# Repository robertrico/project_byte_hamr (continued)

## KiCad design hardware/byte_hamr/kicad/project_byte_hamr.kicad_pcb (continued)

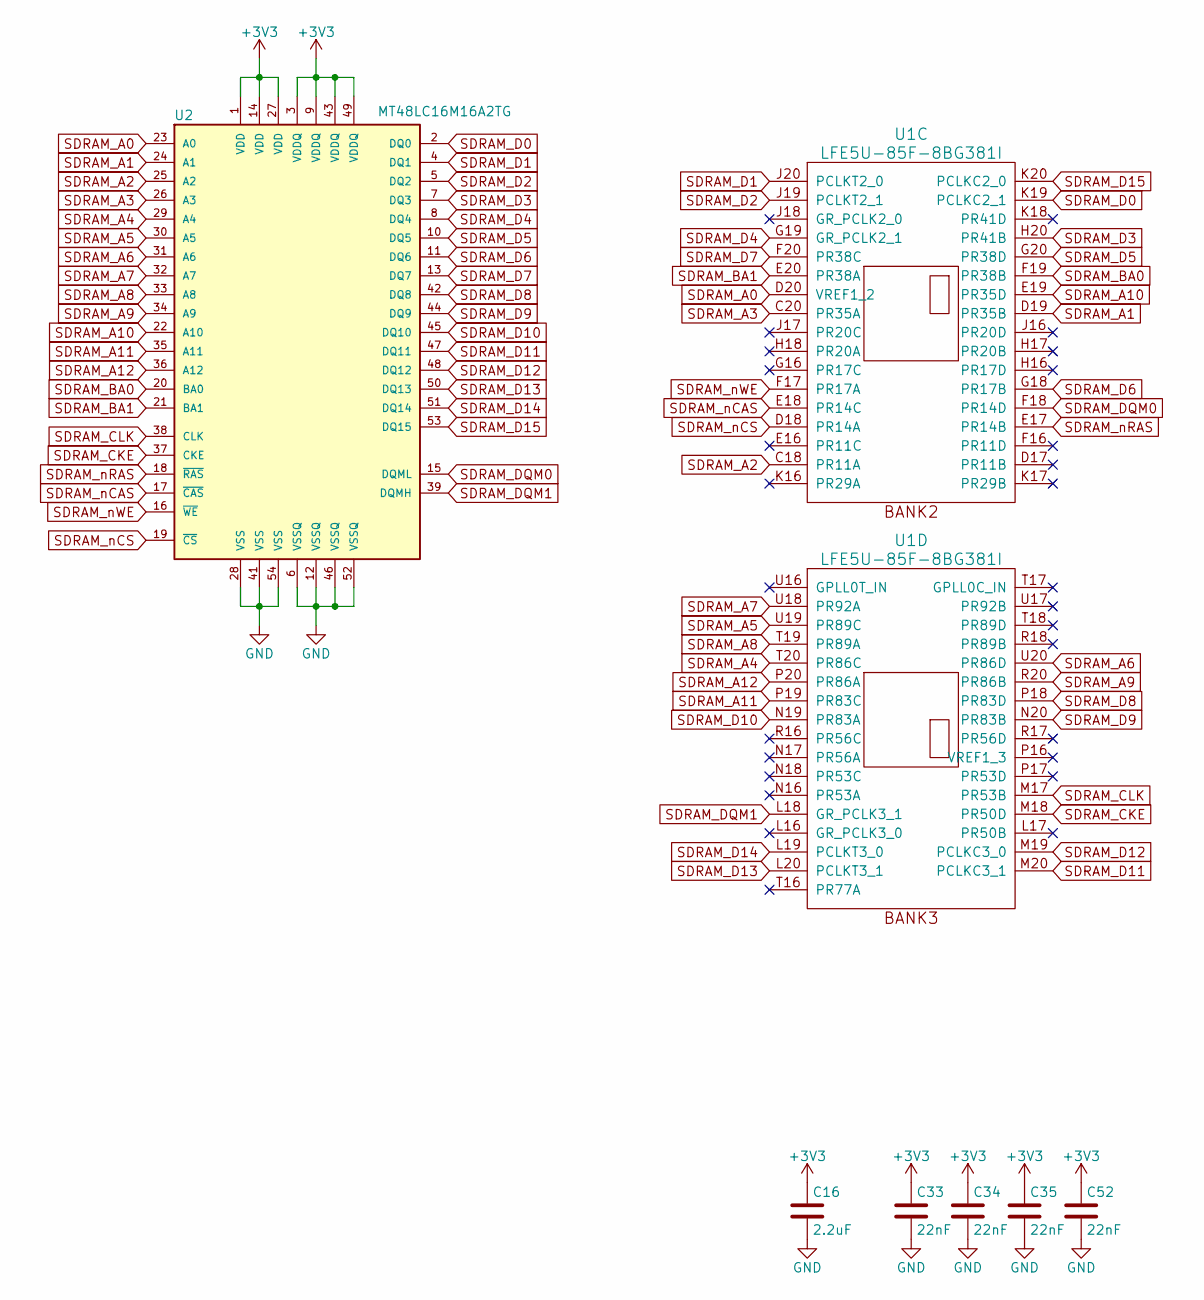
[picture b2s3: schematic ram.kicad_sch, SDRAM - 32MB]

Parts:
C16: 2.2uF; C_0805_2012Metric; MPN CL21B225KOFNNNE
C33, C34, C35, C52: 22nF; C_0603_1608Metric; MPN CX0603MRX7R8BB223
U1: LFE5U-85F-8BG381I; BGA-381_pitch0.8mm_dia0.4mm; MPN LFE5U-85F-8BG381I
U2: MT48LC16M16A2TG; TSOP54; MPN AS4C32M16SB-7TCNTR

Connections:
+3V3: C16.1, C33.1, C34.1, C35.1, C52.1, U2.1 (VDD), U2.3 (VDDQ), U2.9 (VDDQ), U2.14 (VDD), U2.27 (VDD), U2.43 (VDDQ), U2.49 (VDDQ); also elsewhere on the board
GND: C16.2, C33.2, C34.2, C35.2, C52.2, U2.6 (VSSQ), U2.12 (VSSQ), U2.28 (VSS), U2.41 (VSS), U2.46 (VSSQ), U2.52 (VSSQ), U2.54 (VSS); also elsewhere on the board
SDRAM_A0: U1.D20 (VREF1_2), U2.23 (A0)
SDRAM_A1: U1.D19 (PR35B), U2.24 (A1)
SDRAM_A2: U1.C18 (PR11A), U2.25 (A2)
SDRAM_A3: U1.C20 (PR35A), U2.26 (A3)
SDRAM_A4: U1.T20 (PR86C), U2.29 (A4)
SDRAM_A5: U1.U19 (PR89C), U2.30 (A5)
SDRAM_A6: U1.U20 (PR86D), U2.31 (A6)
SDRAM_A7: U1.U18 (PR92A), U2.32 (A7)
SDRAM_A8: U1.T19 (PR89A), U2.33 (A8)
SDRAM_A9: U1.R20 (PR86B), U2.34 (A9)
SDRAM_A10: U1.E19 (PR35D), U2.22 (A10)
SDRAM_A11: U1.P19 (PR83C), U2.35 (A11)
SDRAM_A12: U1.P20 (PR86A), U2.36 (A12)
SDRAM_BA0: U1.F19 (PR38B), U2.20 (BA0)
SDRAM_BA1: U1.E20 (PR38A), U2.21 (BA1)
SDRAM_CKE: U1.M18 (PR50D), U2.37 (CKE)
SDRAM_CLK: U1.M17 (PR53B), U2.38 (CLK)
SDRAM_D0: U1.K19 (PCLKC2_1), U2.2 (DQ0)
SDRAM_D1: U1.J20 (PCLKT2_0), U2.4 (DQ1)
SDRAM_D2: U1.J19 (PCLKT2_1), U2.5 (DQ2)
SDRAM_D3: U1.H20 (PR41B), U2.7 (DQ3)
SDRAM_D4: U1.G19 (GR_PCLK2_1), U2.8 (DQ4)
SDRAM_D5: U1.G20 (PR38D), U2.10 (DQ5)
SDRAM_D6: U1.G18 (PR17B), U2.11 (DQ6)
SDRAM_D7: U1.F20 (PR38C), U2.13 (DQ7)
SDRAM_D8: U1.P18 (PR83D), U2.42 (DQ8)
SDRAM_D9: U1.N20 (PR83B), U2.44 (DQ9)
SDRAM_D10: U1.N19 (PR83A), U2.45 (DQ10)
SDRAM_D11: U1.M20 (PCLKC3_1), U2.47 (DQ11)
SDRAM_D12: U1.M19 (PCLKC3_0), U2.48 (DQ12)
SDRAM_D13: U1.L20 (PCLKT3_1), U2.50 (DQ13)
SDRAM_D14: U1.L19 (PCLKT3_0), U2.51 (DQ14)
SDRAM_D15: U1.K20 (PCLKC2_0), U2.53 (DQ15)
SDRAM_DQM0: U1.F18 (PR14D), U2.15 (DQML)
SDRAM_DQM1: U1.L18 (GR_PCLK3_1), U2.39 (DQMH)
SDRAM_nCAS: U1.E18 (PR14C), U2.17 (~CAS)
SDRAM_nCS: U1.D18 (PR14A), U2.19 (~CS)
SDRAM_nRAS: U1.E17 (PR14B), U2.18 (~RAS)
SDRAM_nWE: U1.F17 (PR17A), U2.16 (~WE)

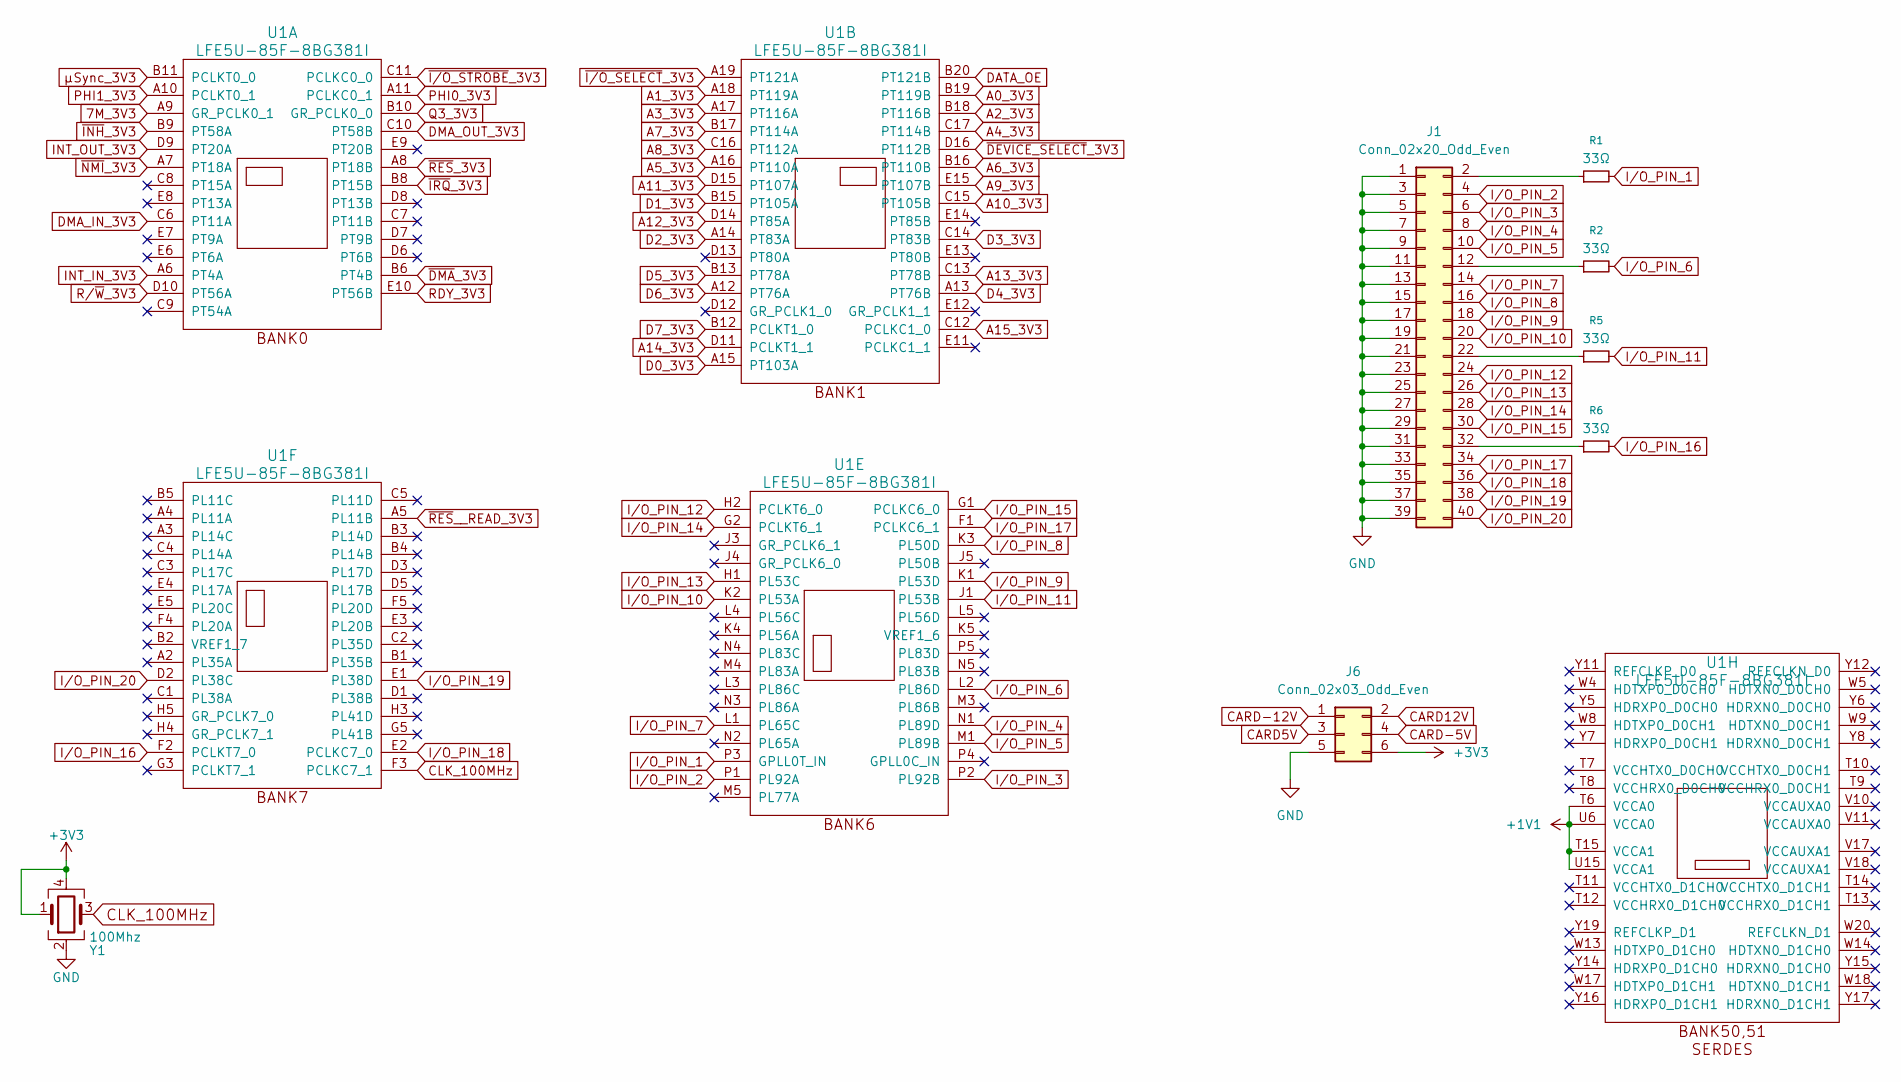
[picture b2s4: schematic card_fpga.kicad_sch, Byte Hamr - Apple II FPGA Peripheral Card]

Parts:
J1: Conn_02x20_Odd_Even; PinHeader_2x20_P2.54mm_Vertical
J6: Conn_02x03_Odd_Even; PinHeader_2x03_P2.54mm_Vertical
R1, R2, R5, R6: 33Ω; R_0603_1608Metric; MPN 0603WAF330JT5E
U1: LFE5U-85F-8BG381I; BGA-381_pitch0.8mm_dia0.4mm; MPN LFE5U-85F-8BG381I
Y1: 100Mhz; Crystal_SMD_7050_4Pads; MPN CWX813-100.0M

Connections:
7M_3V3: U1.A9 (GR_PCLK0_1); also elsewhere on the board
+1V1: U1.T6 (VCCA0), U1.T15 (VCCA1), U1.U6 (VCCA0), U1.U15 (VCCA1); also elsewhere on the board
+3V3: J6.6, Y1.1, Y1.4; also elsewhere on the board
A0_3V3: U1.B19 (PT119B); also elsewhere on the board
A1_3V3: U1.A18 (PT119A); also elsewhere on the board
A2_3V3: U1.B18 (PT116B); also elsewhere on the board
A3_3V3: U1.A17 (PT116A); also elsewhere on the board
A4_3V3: U1.C17 (PT114B); also elsewhere on the board
A5_3V3: U1.A16 (PT110A); also elsewhere on the board
A6_3V3: U1.B16 (PT110B); also elsewhere on the board
A7_3V3: U1.B17 (PT114A); also elsewhere on the board
A8_3V3: U1.C16 (PT112A); also elsewhere on the board
A9_3V3: U1.E15 (PT107B); also elsewhere on the board
A10_3V3: U1.C15 (PT105B); also elsewhere on the board
A11_3V3: U1.D15 (PT107A); also elsewhere on the board
A12_3V3: U1.D14 (PT85A); also elsewhere on the board
A13_3V3: U1.C13 (PT78B); also elsewhere on the board
A14_3V3: U1.D11 (PCLKT1_1); also elsewhere on the board
A15_3V3: U1.C12 (PCLKC1_0); also elsewhere on the board
CARD5V: J6.3; also elsewhere on the board
CARD12V: J6.2; also elsewhere on the board
CARD-5V: J6.4; also elsewhere on the board
CARD-12V: J6.1; also elsewhere on the board
CLK_100MHz: U1.F3 (PCLKC7_1), Y1.3
D0_3V3: U1.A15 (PT103A); also elsewhere on the board
D1_3V3: U1.B15 (PT105A); also elsewhere on the board
D2_3V3: U1.A14 (PT83A); also elsewhere on the board
D3_3V3: U1.C14 (PT83B); also elsewhere on the board
D4_3V3: U1.A13 (PT76B); also elsewhere on the board
D5_3V3: U1.B13 (PT78A); also elsewhere on the board
D6_3V3: U1.A12 (PT76A); also elsewhere on the board
D7_3V3: U1.B12 (PCLKT1_0); also elsewhere on the board
DATA_OE: U1.B20 (PT121B); also elsewhere on the board
DMA_IN_3V3: U1.C6 (PT11A); also elsewhere on the board
DMA_OUT_3V3: U1.C10 (PT58B); also elsewhere on the board
GND: J1.1, J1.3, J1.5, J1.7, J1.9, J1.11, J1.13, J1.15, J1.17, J1.19, J1.21, J1.23, J1.25, J1.27, J1.29, J1.31, J1.33, J1.35, J1.37, J1.39, J6.5, Y1.2; also elsewhere on the board
INT_IN_3V3: U1.A6 (PT4A); also elsewhere on the board
INT_OUT_3V3: U1.D9 (PT20A); also elsewhere on the board
I/O_PIN_1: R1.2, U1.P3 (GPLL0T_IN)
I/O_PIN_2: J1.4, U1.P1 (PL92A)
I/O_PIN_3: J1.6, U1.P2 (PL92B)
I/O_PIN_4: J1.8, U1.N1 (PL89D)
I/O_PIN_5: J1.10, U1.M1 (PL89B)
I/O_PIN_6: R2.2, U1.L2 (PL86D)
I/O_PIN_7: J1.14, U1.L1 (PL65C)
I/O_PIN_8: J1.16, U1.K3 (PL50D)
I/O_PIN_9: J1.18, U1.K1 (PL53D)
I/O_PIN_10: J1.20, U1.K2 (PL53A)
I/O_PIN_11: R5.2, U1.J1 (PL53B)
I/O_PIN_12: J1.24, U1.H2 (PCLKT6_0)
I/O_PIN_13: J1.26, U1.H1 (PL53C)
I/O_PIN_14: J1.28, U1.G2 (PCLKT6_1)
I/O_PIN_15: J1.30, U1.G1 (PCLKC6_0)
I/O_PIN_16: R6.2, U1.F2 (PCLKT7_0)
I/O_PIN_17: J1.34, U1.F1 (PCLKC6_1)
I/O_PIN_18: J1.36, U1.E2 (PCLKC7_0)
I/O_PIN_19: J1.38, U1.E1 (PL38D)
I/O_PIN_20: J1.40, U1.D2 (PL38C)
unnamed: J1.2, R1.1
unnamed: J1.12, R2.1
unnamed: J1.22, R5.1
unnamed: J1.32, R6.1
PHI0_3V3: U1.A11 (PCLKC0_1); also elsewhere on the board
PHI1_3V3: U1.A10 (PCLKT0_1); also elsewhere on the board
Q3_3V3: U1.B10 (GR_PCLK0_0); also elsewhere on the board
RDY_3V3: U1.E10 (PT56B); also elsewhere on the board
R/~W_3V3: U1.D10 (PT56A); also elsewhere on the board
~DEVICE_SELECT_3V3: U1.D16 (PT112B); also elsewhere on the board
~DMA_3V3: U1.B6 (PT4B); also elsewhere on the board
~INH_3V3: U1.B9 (PT58A); also elsewhere on the board
~IRQ_3V3: U1.B8 (PT15B); also elsewhere on the board
~I/O_SELECT_3V3: U1.A19 (PT121A); also elsewhere on the board
~I/O_STROBE_3V3: U1.C11 (PCLKC0_0); also elsewhere on the board
~NMI_3V3: U1.A7 (PT18A); also elsewhere on the board
~RES_3V3: U1.A8 (PT18B); also elsewhere on the board
~RES__READ_3V3: U1.A5 (PL11B); also elsewhere on the board
µSync_3V3: U1.B11 (PCLKT0_0); also elsewhere on the board

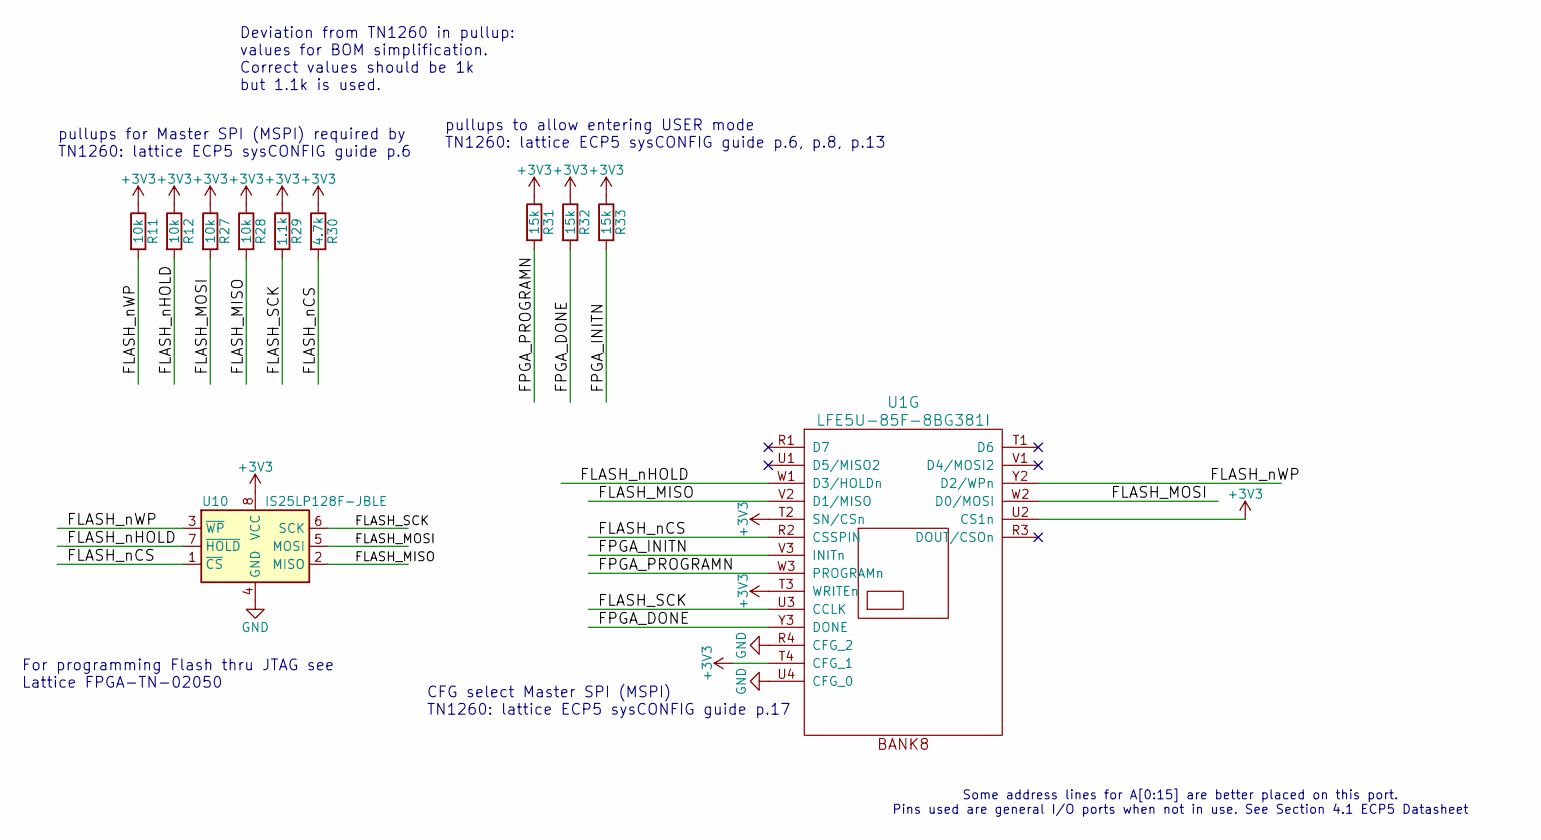
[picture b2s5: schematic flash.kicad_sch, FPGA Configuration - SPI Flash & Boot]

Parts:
R11, R12, R27, R28: 10k; R_0603_1608Metric; MPN AF0603FR-0710KL
R29: 1.1k; R_0603_1608Metric; MPN 0603WAF1101T5E
R30: 4.7k; R_0603_1608Metric; MPN AC0603FR-104K7L
R31, R32, R33: 15k; R_0603_1608Metric; MPN RC0603FR-0715KL
U1: LFE5U-85F-8BG381I; BGA-381_pitch0.8mm_dia0.4mm; MPN LFE5U-85F-8BG381I
U10: IS25LP128F-JBLE; SOA008-150-208mil; MPN IS25LP128F-JBLE

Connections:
+3V3: R11.1, R12.1, R27.1, R28.1, R29.1, R30.1, R31.1, R32.1, R33.1, U1.T2 (SN/CSn), U1.T3 (WRITEn), U1.T4 (CFG_1), U1.U2 (CS1n), U10.8 (VCC); also elsewhere on the board
/flash/FLASH_MISO: R28.2, U1.V2 (D1/MISO), U10.2 (MISO)
/flash/FLASH_MOSI: R27.2, U1.W2 (D0/MOSI), U10.5 (MOSI)
/flash/FLASH_SCK: R29.2, U1.U3 (CCLK), U10.6 (SCK)
/flash/FLASH_nCS: R30.2, U1.R2 (CSSPIN), U10.1 (~CS)
/flash/FLASH_nHOLD: R12.2, U1.W1 (D3/HOLDn), U10.7 (~HOLD)
/flash/FLASH_nWP: R11.2, U1.Y2 (D2/WPn), U10.3 (~WP)
/flash/FPGA_DONE: R32.2, U1.Y3 (DONE)
/flash/FPGA_INITN: R33.2, U1.V3 (INITn)
/flash/FPGA_PROGRAMN: R31.2, U1.W3 (PROGRAMn)
GND: U1.R4 (CFG_2), U1.U4 (CFG_0), U10.4 (GND); also elsewhere on the board

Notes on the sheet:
pullups to allow entering USER mode TN1260: lattice ECP5 sysCONFIG guide p.6, p.8, p.13
pullups for Master SPI (MSPI) required by TN1260: lattice ECP5 sysCONFIG guide p.6
Some address lines for A[0:15] are better placed on this port. Pins used are general I/O ports when not in use. See Section 4.1 ECP5 Datasheet
Deviation from TN1260 in pullup: values for BOM simplification. Correct values should be 1k but 1.1k is used.
CFG select Master SPI (MSPI) TN1260: lattice ECP5 sysCONFIG guide p.17
For programming Flash thru JTAG see Lattice FPGA-TN-02050

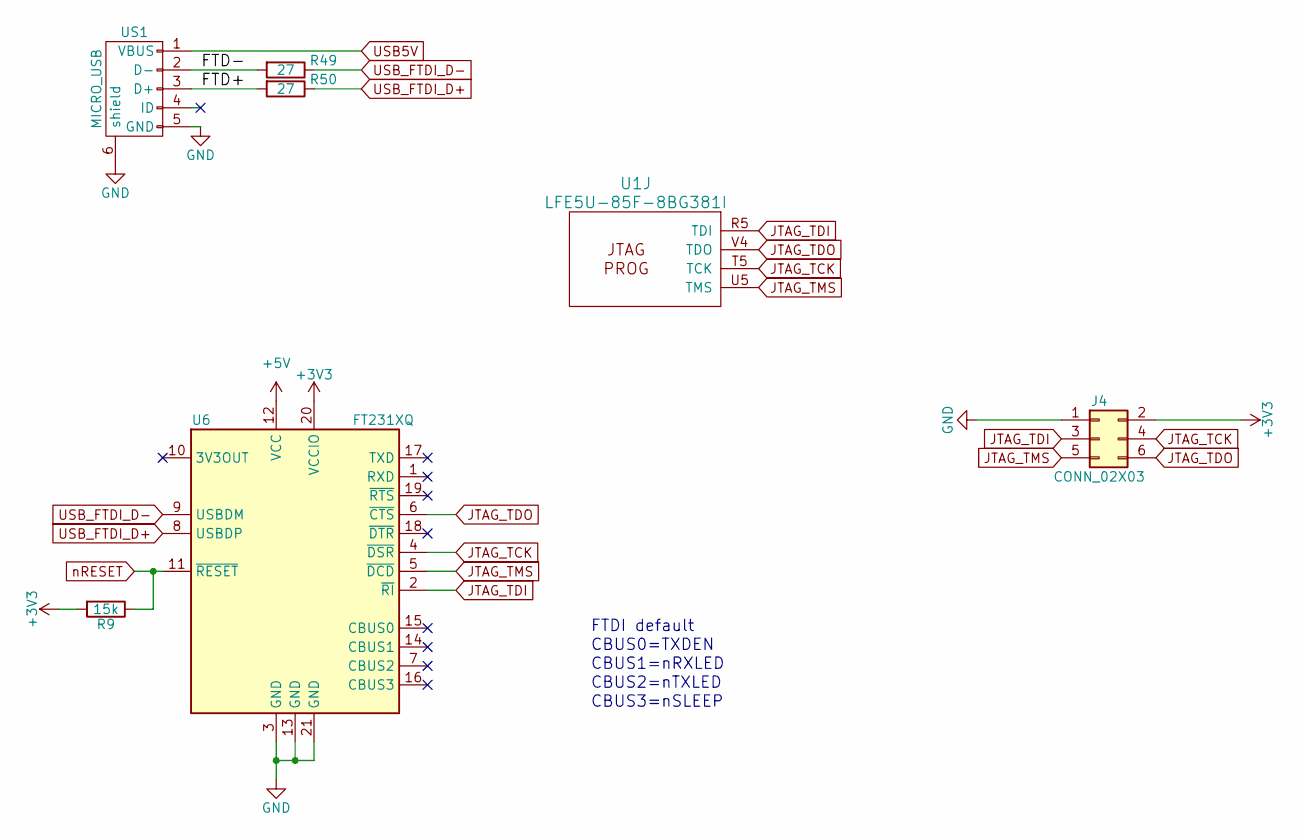
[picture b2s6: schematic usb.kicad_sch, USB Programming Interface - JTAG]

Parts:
J4: CONN_02X03; PinHeader_2x03_P2.54mm_Vertical
R9: 15k; R_0603_1608Metric; MPN RC0603FR-0715KL
R49, R50: 27; R_0603_1608Metric; MPN RC0603FR-0727RL
U1: LFE5U-85F-8BG381I; BGA-381_pitch0.8mm_dia0.4mm; MPN LFE5U-85F-8BG381I
U6: FT231XQ; FT231X-QFN-20-1EP_4x4mm_P0.5mm_EP2x2mm; MPN FT231XQ-R
US1: MICRO_USB; USB-MICRO-B-FCI-10118192-0001LF; MPN 10118192-0001LF

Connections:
+3V3: J4.2, R9.2, U6.20 (VCCIO); also elsewhere on the board
+5V: U6.12 (VCC); also elsewhere on the board
/usb/FTD+: R50.2, US1.3 (D+)
/usb/FTD-: R49.2, US1.2 (D-)
GND: J4.1, U6.3 (GND), U6.13 (GND), U6.21 (GND), US1.5 (GND), US1.6 (shield); also elsewhere on the board
JTAG_TCK: J4.4, U1.T5 (TCK), U6.4 (~DSR)
JTAG_TDI: J4.3, U1.R5 (TDI), U6.2 (~RI)
JTAG_TDO: J4.6, U1.V4 (TDO), U6.6 (~CTS)
JTAG_TMS: J4.5, U1.U5 (TMS), U6.5 (~DCD)
USB5V: US1.1 (VBUS); also elsewhere on the board
USB_FTDI_D+: R50.1, U6.8 (USBDP)
USB_FTDI_D-: R49.1, U6.9 (USBDM)
nRESET: R9.1, U6.11 (~RESET)

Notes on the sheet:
FTDI default
CBUS0=TXDEN
CBUS3=nSLEEP
CBUS2=nTXLED
CBUS1=nRXLED

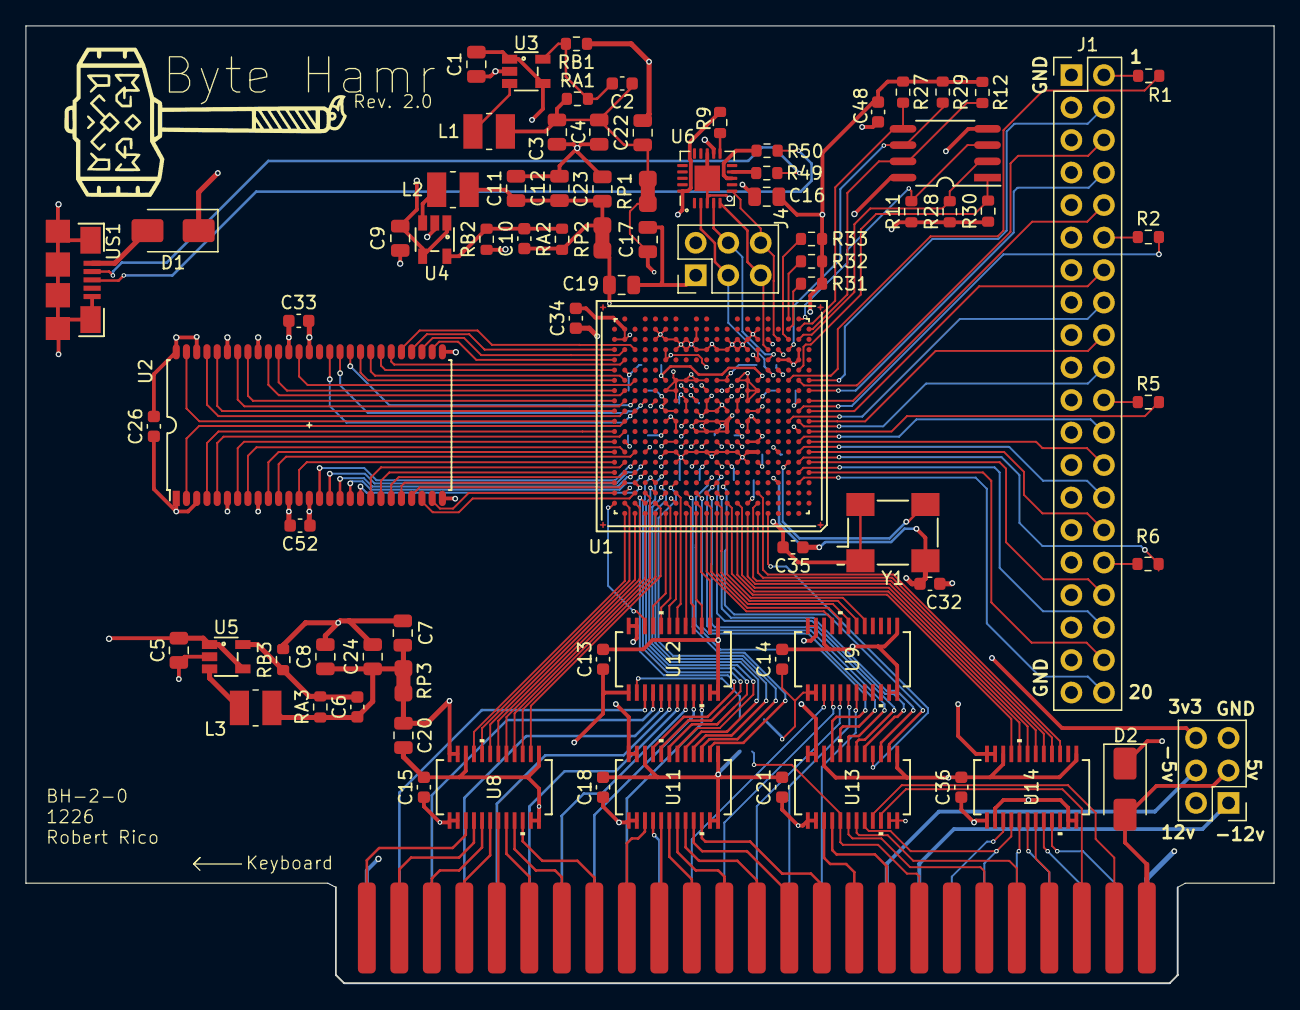
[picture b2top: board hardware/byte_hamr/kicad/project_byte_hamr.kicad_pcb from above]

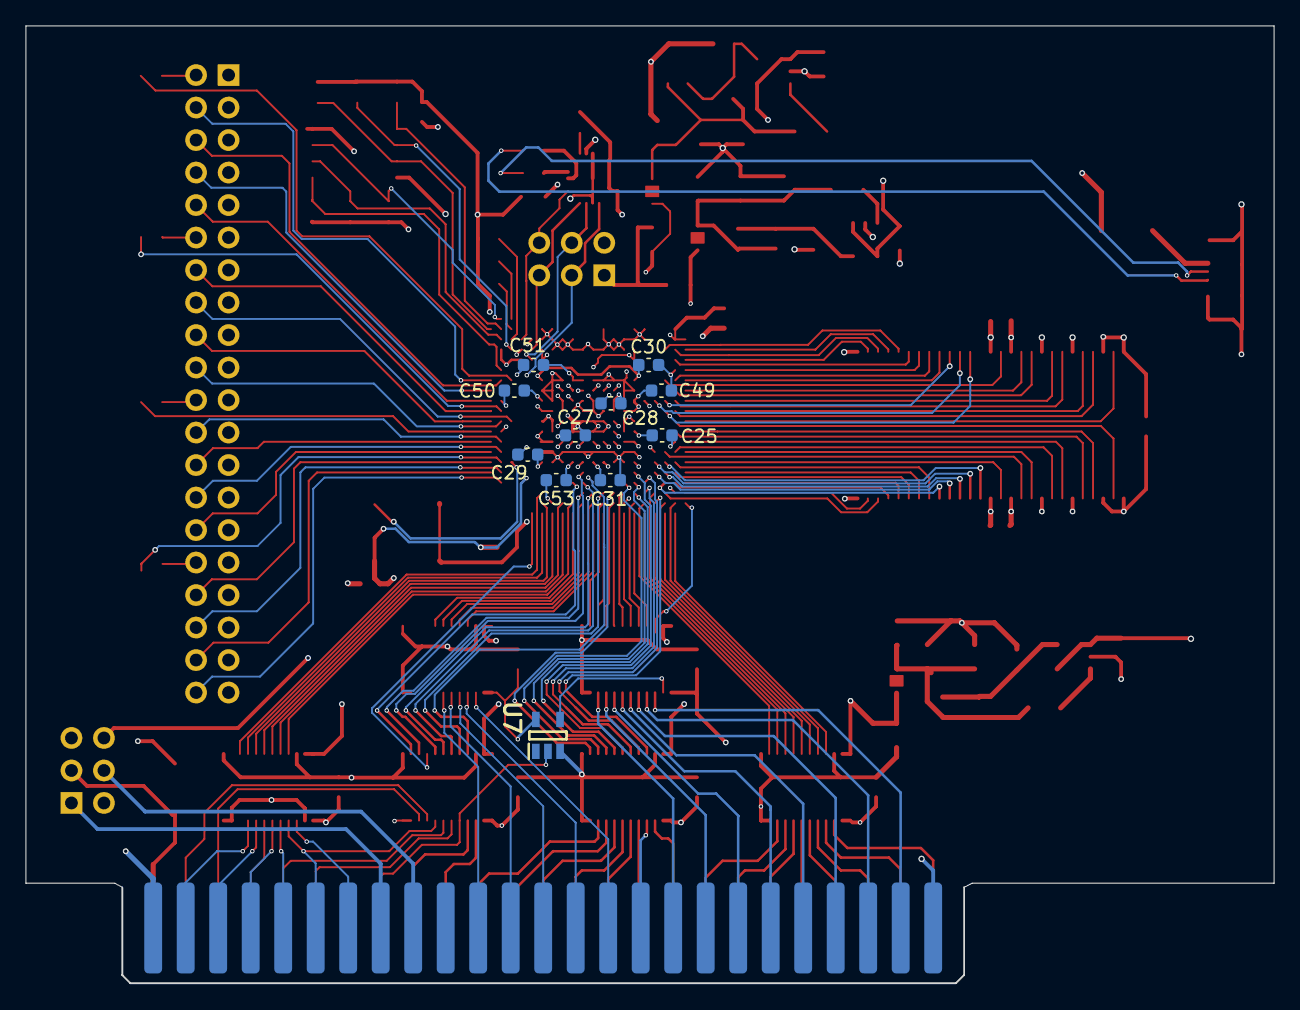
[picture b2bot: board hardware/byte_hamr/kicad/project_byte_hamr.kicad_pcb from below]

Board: 4 copper layers, 97.6 x 74.8 mm, 92 parts (11 on the bottom side), 190 nets.

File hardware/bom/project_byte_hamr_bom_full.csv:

Id,Designator,Footprint,Quantity,Designation,Supplier and ref,Notes:
1,U1,BGA-381_pitch0.8mm_dia0.4mm,1,LFE5U-85F-8BG381I,Lattice Semiconductor :: LFE5U-85F-8BG381I,FPGA w/ BGA
2,"C30,C51,C26,C27,C25,C33,C32,C50,C31,C28,C13,C53,C29,C18,C15,C36,C21,C52,C49,C35,C34,C14,C48",C_0603_1608Metric,23,22nF,Samsung Electro-Mechanics :: CL10B223KA8NNWC,Please provide standard or equivalent parts if needed.
3,"R49,R50",R_0603_1608Metric,2,27,YAGEO :: RC0603FR-0727RL,Please provide standard or equivalent parts if needed.
4,"R9,R32,RA2,RA3,RA1,R33,R31",R_0603_1608Metric,7,15k,YAGEO :: AC0603FR-0715KL,Please provide standard or equivalent parts if needed.
5,"R1,R37",R_0603_1608Metric,2,549,YAGEO :: RC0603FR-07549RL,Please provide standard or equivalent parts if needed.
6,D3,LED_0805_2012Metric,1,YELLOW,Lite-On Inc. :: LTST-C170KRKT,Please provide standard or equivalent parts if needed.
7,"U5,U3,U4",TSOT-25,3,TLV62569DBV,Texas Instruments :: TLV62569DBVR,Please provide replacement if needed.
8,"R11,R12,R28,R27",R_0603_1608Metric,4,10k,YAGEO :: AF0603FR-0710KL,Please provide standard or equivalent parts if needed.
9,"U13,U8,U9,U12,U11,U14",DBQ24-L,6,SN74LVC8T245,Texas Instruments :: SN74LVC8T245DBQR,Please provide standard or equivalent parts if needed.
10,"C12,C1,C5,C7,C3,C8,C4,C9,C11",C_0805_2012Metric,9,22uF,Samsung Electro-Mechanics :: CAP CER 22UF 6.3V X5R 0805,Please provide standard or equivalent parts if needed.
11,RB3,R_0603_1608Metric,1,3.3k,YAGEO :: AC0603FR-073K3L,Please provide standard or equivalent parts if needed.
12,"RP3,RP1,RP2",R_0805_2012Metric_Pad1.29x1.40mm_HandSolder_Jumper_NC,3,0,YAGEO :: RC0805JR-070RP,This can be left off. But I do want to make sure the two sides of the nets are connected.
13,"C10,C2,C6",C_0603_1608Metric,3,100pF,YAGEO :: CC0603KRX7R8BB101,Please provide standard or equivalent parts if needed.
14,R29,R_0603_1608Metric,1,1.1k,Panasonic Electronic Components :: RES SMD 1.1K OHM 1% 1/10W 0603,Please provide standard or equivalent parts if needed.
15,"C22,C16,C20,C17,C19,C24,C23",C_0805_2012Metric,7,2.2uF,Taiyo Yuden :: LMK212BJ225KG-T,Please provide standard or equivalent parts if needed.
16,D19,LED_0805_2012Metric,1,RED,Lite-On Inc. :: LTST-C170KRKT,Please provide standard or equivalent parts if needed.
17,"D2,D1",D_SMA,2,STPS2L40AF,STMicroelectronics :: STPS2L40AF,Please provide standard or equivalent parts if needed.
18,RB1,R_0603_1608Metric,1,18k,YAGEO :: RC0603FR-0718KL,Please provide standard or equivalent parts if needed.
19,"L1,L2,L3",L_1008_1210,3,2.2uH,Murata Electronics :: DFE322520FD-2R2M=P2,Please provide standard or equivalent parts if needed.
20,US1,USB-MICRO-B-FCI-10118192-0001LF,1,MICRO_USB,Amphenol ICC (FCI) :: 10118192-0001LF,Please provide standard or equivalent parts if needed.
21,U10,SOA008-150-208mil,1,IS25LP128F-JBLE,"ISSI, Integrated Silicon Solution Inc :: IC FLASH 128MBIT SPI/QUAD 8SOIC",Please provide replacement if needed.
22,J4,PinHeader_2x03_P2.54mm_Vertical,1,CONN_02X03,-,"Connector Pins, I will solder on."
23,U2,TSOP54,1,AS4C32M16SB-7TCNTR,"Alliance Memory, Inc. :: AS4C32M16SB-7TCNTR",Please provide replacement if needed.
24,U6,FT231X-QFN-20-1EP_4x4mm_P0.5mm_EP2x2mm,1,FT231XQ,"FTDI, Future Technology Devices International Ltd :: FT231XQ-R",Please provide replacement if needed.
25,"R30,RB2",R_0603_1608Metric,2,4.7k,YAGEO :: AC0603FR-074K7L,Please provide standard or equivalent parts if needed.
26,Y1,Crystal_SMD_7050_4Pads,1,FNETHE025,Diodes Incorporated :: FNETHE025,Please provide standard or equivalent parts if needed.
27,J1,Connector_PinHeader_2.54mm:PinHeader_1x13_P2.54mm_Horizontal,1,PinHeader_1x13,-,"Connector Pins, I will solder on."

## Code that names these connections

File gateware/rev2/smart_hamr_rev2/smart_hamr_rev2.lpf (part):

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//
// Per-design overrides (matching the daughter-board GPIO assignment in
// smart_hamr_top.v):
//   GPIO_1  (debug nDEVICE_SELECT):   SLEWRATE=FAST   (clean LA edges)
//   GPIO_10 (wrdata, FPGA → ESP32):   SLEWRATE=FAST   PULLMODE=NONE
//   GPIO_12 (rddata, ESP32 → FPGA):   PULLMODE=DOWN   (matches ESP32 idle-LOW)
//   GPIO_13 (sense,  ESP32 → FPGA):   PULLMODE=UP     (defined idle when
//                                                      ESP32 not driving)
//
// All other pins identical to base byte_hamr.lpf.
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// =============================================================================
// GPIO Header (Smart Hamr / FujiNet bridge)
// =============================================================================
LOCATE COMP "GPIO_1"  SITE "P3";
IOBUF PORT "GPIO_1"  IO_TYPE=LVCMOS33 DRIVE=8 SLEWRATE=FAST PULLMODE=NONE;   // /DEV debug → LA (damped pad, fine for slow probe)
LOCATE COMP "GPIO_2"  SITE "P1";
IOBUF PORT "GPIO_2"  IO_TYPE=LVCMOS33 DRIVE=8 SLEWRATE=SLOW PULLMODE=NONE;   // unused
LOCATE COMP "GPIO_3"  SITE "P2";
IOBUF PORT "GPIO_3"  IO_TYPE=LVCMOS33 DRIVE=8 SLEWRATE=SLOW PULLMODE=NONE;   // unused
LOCATE COMP "GPIO_4"  SITE "N1";
IOBUF PORT "GPIO_4"  IO_TYPE=LVCMOS33 DRIVE=8 SLEWRATE=SLOW PULLMODE=NONE;   // unused
LOCATE COMP "GPIO_5"  SITE "M1";
IOBUF PORT "GPIO_5"  IO_TYPE=LVCMOS33 DRIVE=8 SLEWRATE=SLOW PULLMODE=NONE;   // unused
LOCATE COMP "GPIO_6"  SITE "L2";
IOBUF PORT "GPIO_6"  IO_TYPE=LVCMOS33 DRIVE=8 SLEWRATE=SLOW PULLMODE=NONE;   // unused (damped)
LOCATE COMP "GPIO_7"  SITE "L1";
IOBUF PORT "GPIO_7"  IO_TYPE=LVCMOS33 DRIVE=8 SLEWRATE=SLOW PULLMODE=NONE;   // unused
LOCATE COMP "GPIO_8"  SITE "K3";
IOBUF PORT "GPIO_8"  IO_TYPE=LVCMOS33 DRIVE=8 SLEWRATE=SLOW PULLMODE=NONE;   // unused
LOCATE COMP "GPIO_9"  SITE "K1";
IOBUF PORT "GPIO_9"  IO_TYPE=LVCMOS33 DRIVE=8 SLEWRATE=SLOW PULLMODE=NONE;   // _enbl2
LOCATE COMP "GPIO_10" SITE "K2";
IOBUF PORT "GPIO_10" IO_TYPE=LVCMOS33 DRIVE=8 SLEWRATE=FAST PULLMODE=NONE;   // wrdata (fast slew)
LOCATE COMP "GPIO_11" SITE "J1";
IOBUF PORT "GPIO_11" IO_TYPE=LVCMOS33 DRIVE=8 SLEWRATE=SLOW PULLMODE=NONE;   // unused (damped)
// Input (ESP32 → FPGA):
LOCATE COMP "GPIO_12" SITE "H2";
IOBUF PORT "GPIO_12" IO_TYPE=LVCMOS33 PULLMODE=DOWN;                          // rddata (idle LOW)
LOCATE COMP "GPIO_13" SITE "H1";
IOBUF PORT "GPIO_13" IO_TYPE=LVCMOS33 PULLMODE=UP;                            // sense/ACK (idle high)
// Outputs continued:
LOCATE COMP "GPIO_14" SITE "G2";
IOBUF PORT "GPIO_14" IO_TYPE=LVCMOS33 DRIVE=8 SLEWRATE=SLOW PULLMODE=NONE;   // _wrreq
LOCATE COMP "GPIO_15" SITE "G1";
IOBUF PORT "GPIO_15" IO_TYPE=LVCMOS33 DRIVE=8 SLEWRATE=SLOW PULLMODE=NONE;   // phase[1]
LOCATE COMP "GPIO_16" SITE "F2";
IOBUF PORT "GPIO_16" IO_TYPE=LVCMOS33 DRIVE=8 SLEWRATE=SLOW PULLMODE=NONE;   // phase[0] (damped, OK for phase)
LOCATE COMP "GPIO_17" SITE "F1";
IOBUF PORT "GPIO_17" IO_TYPE=LVCMOS33 DRIVE=8 SLEWRATE=SLOW PULLMODE=NONE;   // phase[3]
LOCATE COMP "GPIO_18" SITE "E2";
IOBUF PORT "GPIO_18" IO_TYPE=LVCMOS33 DRIVE=8 SLEWRATE=SLOW PULLMODE=NONE;   // phase[2]
LOCATE COMP "GPIO_19" SITE "E1";
IOBUF PORT "GPIO_19" IO_TYPE=LVCMOS33 DRIVE=8 SLEWRATE=SLOW PULLMODE=NONE;   // unused
LOCATE COMP "GPIO_20" SITE "D2";
IOBUF PORT "GPIO_20" IO_TYPE=LVCMOS33 DRIVE=8 SLEWRATE=SLOW PULLMODE=NONE;   // _enbl1

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
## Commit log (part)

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2026-03-19 PnP File
2026-03-20 IWM Hamr WIP
    Not A bootable Disk achieved.
2026-03-25 Add SmartPort test disk images
    Includes a collection of ProDOS-order (.po) disk images designed to test SmartPort functionality. These files provide test vectors for multi-block transfers, checksum verification, and various data p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
2026-03-25 IWM Hamr v1
    IWM Hamr: snapshot before architecture pivot
2026-03-31 Add read-flash and write-flash targets to Makefile
    Provide a mechanism to back up the SPI flash disk image to a file and write new images directly via the JTAG loader. Defaults to the 12MB maximum volume size to match the current hardware capacity.
2026-03-31 Add documentation for all Byte Hamr gateware projects
    Provide detailed README.md files for each subdirectory in gateware/, covering register maps, system architecture, usage instructions, and Makefile commands for:
    - Signal Check: Initial board bring-up and sanity testing
    - SDRAM Test/Bank: Linear and bank-switched memory validation
    - Pattern ROM: Test pattern generator for bus/SDRAM verification
    - Logic Hamr: 8-channel logic analyzer with HIRES display regeneration
    - Block Hamr: ProDOS block storage device with SPI flash persistence
2026-04-07 Attempt on, no softcore
2026-04-09 Clean Document Artifact
2026-04-09 Clean house: update hardware specs and remove obsolete artifacts
    - Corrected FPGA LUT count (84K), GPIO pin count (13), and oscillator frequency (25MHz) in documentation.
    - Updated gateware project descriptions and LPF comments to reflect the current PicoRV32 + FatFS architecture.
    - Removed obsolete TODO.md and SmartPort test disk images.
    - Fixed .gitignore case sensitivity for .DS_Store.
2026-04-11 docs: add project-wide documentation for constraints, gateware, and software
    Adds README files describing constraints, gateware design, and software structure to guide future contributors.
2026-04-12 Organize disk images into per-project images/ directories
    - Update .gitignore to exclude per-project images/ directories and FujiNet config.
    - Update Makefiles, build scripts, and assembly source to reference the new images/ paths.
    - Remove binary disk images from repository tracking in favor of local images/ storage.
    - Delete the HANDOFF_v8.md roadmap document.
2026-04-26 Smart Port v2
2026-04-29 WIP: smart_hamr Q7/buffer rework — boots to FujiNet menu
    iwm.v
    - writeCondPrev1/Prev2 pipeline replaced with /DEV-rising-edge sample
    (matches IWM spec). R_nW + addr[0] latched on /DEV-falling alongside
    q7/q6, 2-FF synced into fclk domain for the fire condition. Eliminates
    R_nW-vs-/DEV-rising race that caused buffer-load to miss real STAs.
    - R_nW gate on writeCondNow blocks STA abs,X dummy-read fires that were
2026-04-30 WIP: smart_hamr iwm — DRAIN_DELAY 200µs → 700µs
    Bumped DRAIN_DELAY from 1430 fclk (~200µs) to 5012 fclk (~700µs) and
    widened drain_delay_ctr from 11 to 13 bits to fit the larger value
    without silent truncation.
    Why: bit 6 (_underrun_delayed) of the handshake register at $C0CC is
    polled by Liron's end-of-transmit BVS loop (liron.asm:2153) before
    clearing Q7. On real Apple II IWM hardware this bit had natural analog
2026-05-04 Add smart_hamr_rev2: ASIC-faithful Liron SmartPort emulation
    This new gateware design implements an ASIC-faithful Apple Liron SmartPort controller for Byte Hamr Rev 2. It closely mirrors the IWM ASIC and Liron ROM behavior, bridging the Apple II's IWM register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
    This commit includes all core gateware (IWM ASIC, boot ROM, address decoder), build scripts, and comprehensive documentation (`PLAN.md`, `README.md`, `docs/`). A detailed investigation log (`findings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
2026-06-03 sim: faithful SDRAM model (bounded dense, row@ACTIVE/col@R-W, A10 mask, DQM)
2026-06-03 test: sdram_ctrl unit TB (round-trip, byte-lane, bank isolation)
2026-06-03 plan: record sdram_ctrl as-built deviations (read timing, request-scoped busy)
2026-06-03 plan: record Tasks 5+6 as-built (sticky busy, TB loop fix, mon.mem guard)
2026-06-03 docs: project_obscurus SDRAM monitor memory map + bench checklist
2026-06-03 review: add SIM_MODELS to sim prereq; note unsynced rom_en latch is benign
2026-06-03 plan: sdmdisk rm needs -f (base image files are locked)
2026-06-03 docs: SDM driver library README + bench checklist
2026-06-03 fix(sdmdisk): TXT import --aux 0 (sequential, not L=8192 random-access)
    acx --text defaulted the TXT record length to $2000 (8192), making
    SDRAMLIB a random-access text file. ProDOS copy utilities tried to read a
    full 8192-byte record off a 3123-byte file -> 'no disk in drive'/crash.
    --aux 0 makes it a normal sequential text file (copies + Merlin LOAD/PUT).
2026-06-03 fix(sdmdisk): ship lib as SDRAMLIB.S (Merlin auto-appends .S) + aux 0
    Merlin-Pro Load/Save/PUT auto-append .S, so a disk file named SDRAMLIB
    gives '46 FILE NOT FOUND' on `L SDRAMLIB`. Import as SDRAMLIB.S so
    L/PUT SDRAMLIB resolve it. Keep --aux 0 (sequential) so ProDOS copy
    utilities don't choke on a random-access (L=8192) text file.
2026-06-04 spec: add software contract & timing (data never arms; arm only for $C800 ROM)
2026-06-04 feat: rom_armed soft-switch gates $C800 drive (default silent); sim asserts arm/disarm/magic/reset
2026-06-04 feat: $C400 arms $C800 + DISARM@$C420; monitor T sweep + Q disarms
2026-06-04 docs: armed expansion ROM — arm/disarm protocol, register map, bench checklist
2026-06-05 fix: SEI/CLI around armed session (T crash) + Merlin source tabs/ASCII
    T command crashed (BRK) because the ~1-2s armed sweep let an IRQ fire whose
    handler touched the shared $C800 while we drove it. R/W/B/D survive because
    their armed windows are microseconds. Fix: SEI in the $C400 stub (whole armed
    session), CLI in the $C420 DISARM. GETLN/COUT are polled so nothing breaks.
    Also: reformat all .S to TAB-delimited columns + ASCII-only (was space-aligned
    with UTF-8 em-dashes) so they load correctly in Merlin on the Apple II — the
2026-06-05 build: rename sdmdisk volume to /SDRAM/
2026-06-05 fix: Merlin source = single-space fields (not tabs), matching software/ASM/*.S
    Tabs got high-bit-set to $89 on disk import -> Merlin showed boxes. Real
    project Merlin sources (software/ASM/*.S) use single-space field separators,
    0 tabs, ASCII. Reformat all .S to match. ROM bytes unchanged (whitespace only).
2026-06-05 fix(sdmdisk): fresh /SDRAM/ volume, no delete-reallocate churn
    Deleting base bulk files then re-importing made acx reuse freed blocks, so
    SDRAMLIB.S's first data block landed on a freed COPYIIPLUS block (48) ->
    ProDOS-on-Apple I/O error copying it (block 48), reproducible. Build a fresh
    -pro140 volume + copy boot blocks/PRODOS/BASIC.SYSTEM from base + add our two
    files -> contiguous clean allocation. Keep acx --aux 0 for the sequential TXT.
2026-06-05 fix(SDRAMLIB): SDMBASE expr left-to-right safe (SLOT*16+$C080)
    Merlin-on-Apple evaluates expressions strictly left-to-right with NO precedence,
    so $C080+SLOT*16 = ($C080+4)*16 = $C0840 -> overflow -> OPERAND TOO LONG, and
    every R_xxx = SDMBASE+n inherits it -> error on almost every line. Merlin32
    (precedence) was fine, hiding it. Reorder to SLOT*16+$C080 = $40+$C080 = $C0C0,
    correct under both. Value unchanged -> ROM/binary identical.
2026-06-05 fix(SDRAMLIB): short lines for Merlin-on-Apple (was OPERAND TOO LONG line 1)
    Merlin source line-length limit: our 79-char banner/comment lines tripped
    'OPERAND TOO LONG' (generic over-length error, fires even on * comment lines).
    Working sources top out ~52 chars. Trim banners + comments so every line is
    <=40 chars, uppercase ASCII like software/ASM/*.S. Code/value unchanged ->
    SDMTEST binary identical.
2026-06-12 test(farm): v2 seeds tb - new bank map, crop args, EVPRICE(crop,price) (red)
2026-06-12 test(farm): workshop tb - craft pipeline, dual heartbeat, dual reset (red)
2026-06-15 feat(farm): deposit crop-picker - DEP 1-4? prompt, no hidden SELCROP
2026-06-16 cleanup(farm): drop dead NEED/WPANT equates, WJCOLL->WJSELL, fix stale comments
2026-06-16 feat(farm): bank-33 CVER=3 selective migration + GOODS mirror (preserve recipes/skill)
2026-06-18 test(coproc): remove workshop phases + farm helpers from tb
    Farm+workshop game-logic now fully in FARM_TEST (44 cases green on
    hardware). tb keeps gateware (monitor/hibram/SDRAM/cflash) + C1-C4 kernel
    phases (migrate next). Shared helpers (sdram_read/wr_reg/stage_mbox/ring)
    kept. Compiles clean.
